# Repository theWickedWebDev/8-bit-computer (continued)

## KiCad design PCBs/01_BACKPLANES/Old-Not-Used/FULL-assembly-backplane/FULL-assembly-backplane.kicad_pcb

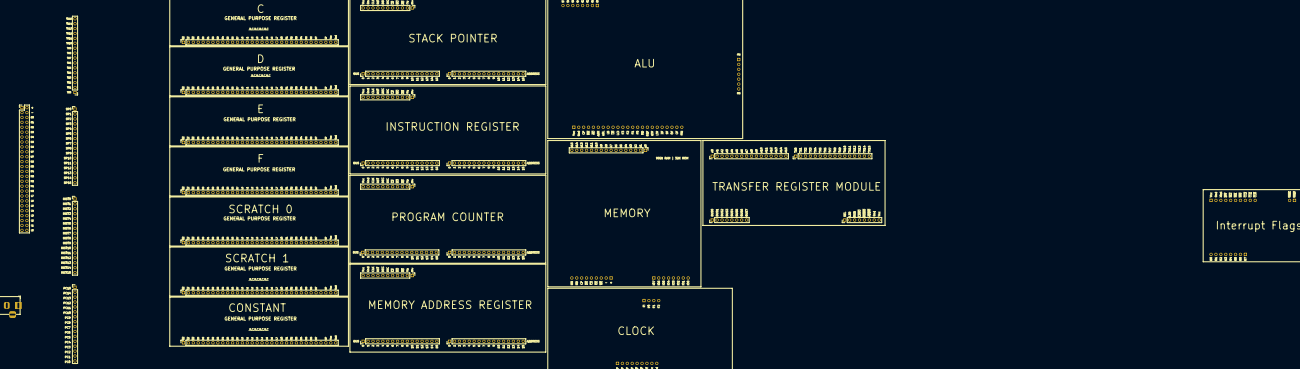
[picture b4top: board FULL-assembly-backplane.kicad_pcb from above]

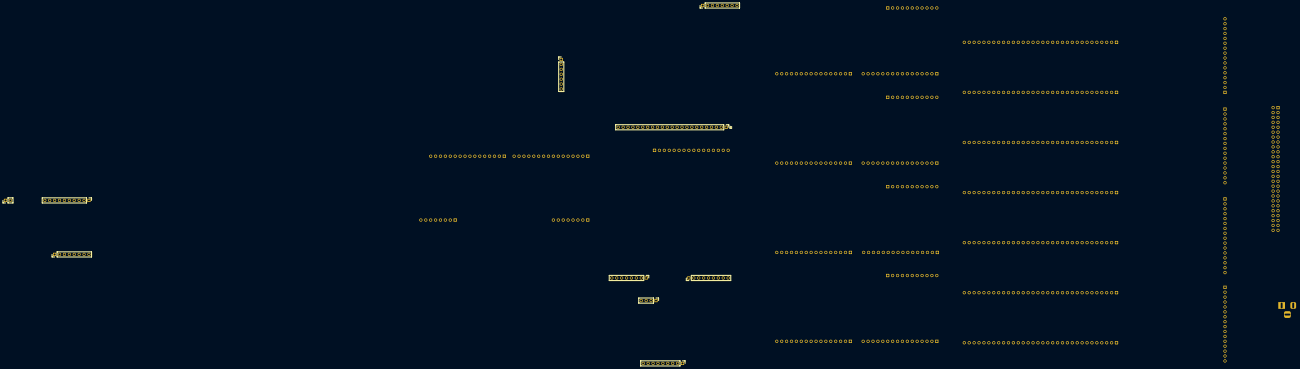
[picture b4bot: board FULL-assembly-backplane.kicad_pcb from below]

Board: 2 copper layers, 40 parts (10 on the bottom side), 108 nets, no tracks yet.

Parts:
J1, J2, J5, J6, J7, J8, J9, J10, J11, J12, J13, J14, J15, J16, J17: Conn_01x16; PinHeader_1x16_P2.54mm_Vertical
J1#2, J2#2: Conn_01x09; PinHeader_1x09_P2.54mm_Vertical
J1#3, J2#3, J2#5, J3, J4: Conn_01x08; PinHeader_1x08_P2.54mm_Vertical
J1#4: Conn_01x04; PinHeader_1x04_P2.54mm_Vertical
J1#5: Conn_01x10; PinHeader_1x10_P2.54mm_Vertical
J2#4: Conn_01x23; PinHeader_1x23_P2.54mm_Vertical
J3#2: Conn_01x07; PinHeader_1x07_P2.54mm_Vertical
J3#3: Conn_01x02; PinHeader_1x02_P2.54mm_Vertical
J18, J19, J20, J21: Conn_01x11; PinHeader_1x11_P2.54mm_Vertical
J25, J26, J32, J33, J34, J35, J36: Conn_01x32; PinSocket_1x32_P2.54mm_Vertical
J37: Conn_01x26; PinHeader_2x26_P2.54mm_Vertical
J43: Barrel_Jack; BarrelJack_Horizontal

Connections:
/IN_B0: J10.1, J11.1
/IN_B1: J10.2, J11.2
/IN_B2: J10.3, J11.3
/IN_B3: J10.4, J11.4
/IN_B4: J10.5, J11.5
/IN_B5: J10.6, J11.6
/IN_B6: J10.7, J11.7
/IN_B7: J10.8, J11.8
/IN_B8: J10.9, J11.9
/IN_B9: J10.10, J11.10
/IN_B10: J10.11, J11.11
/IN_B11: J10.12, J11.12
/IN_B12: J10.13, J11.13
/IN_B13: J10.14, J11.14
/IN_B14: J10.15, J11.15
/IN_B15: J10.16, J11.16
/MAR_B0: J16.1, J17.1
/MAR_B1: J16.2, J17.2
/MAR_B2: J16.3, J17.3
/MAR_B3: J16.4, J17.4
/MAR_B4: J16.5, J17.5
/MAR_B5: J16.6, J17.6
/MAR_B6: J16.7, J17.7
/MAR_B7: J16.8, J17.8
/MAR_B8: J16.9, J17.9
/MAR_B9: J16.10, J17.10
/MAR_B10: J16.11, J17.11
/MAR_B11: J16.12, J17.12
/MAR_B12: J16.13, J17.13
/MAR_B13: J16.14, J17.14
/MAR_B14: J16.15, J17.15
/MAR_B15: J16.16, J17.16
/PC_B0: J13.1, J14.1
/PC_B1: J13.2, J14.2
/PC_B2: J13.3, J14.3
/PC_B3: J13.4, J14.4
/PC_B4: J13.5, J14.5
/PC_B5: J13.6, J14.6
/PC_B6: J13.7, J14.7
/PC_B7: J13.8, J14.8
/PC_B8: J13.9, J14.9
/PC_B9: J13.10, J14.10
/PC_B10: J13.11, J14.11
/PC_B11: J13.12, J14.12
/PC_B12: J13.13, J14.13
/PC_B13: J13.14, J14.14
/PC_B14: J13.15, J14.15
/PC_B15: J13.16, J14.16
/SP_B0: J7.1, J8.1
/SP_B1: J7.2, J8.2
/SP_B2: J7.3, J8.3
/SP_B3: J7.4, J8.4
/SP_B4: J7.5, J8.5
/SP_B5: J7.6, J8.6
/SP_B6: J7.7, J8.7
/SP_B7: J7.8, J8.8
/SP_B8: J7.9, J8.9
/SP_B9: J7.10, J8.10
/SP_B10: J7.11, J8.11
/SP_B11: J7.12, J8.12
/SP_B12: J7.13, J8.13
/SP_B13: J7.14, J8.14
/SP_B14: J7.15, J8.15
/SP_B15: J7.16, J8.16
/TX0: J2.1, J5.1
/TX1: J2.2, J5.2
/TX2: J2.3, J5.3
/TX3: J2.4, J5.4
/TX4: J2.5, J5.5
/TX5: J2.6, J5.6
/TX6: J2.7, J5.7
/TX7: J2.8, J5.8
/TX8: J2.9, J5.9
/TX9: J2.10, J5.10
/TX10: J2.11, J5.11
/TX11: J2.12, J5.12
/TX12: J2.13, J5.13
/TX13: J2.14, J5.14
/TX14: J2.15, J5.15
/TX15: J2.16, J5.16
BUS0: J3.1, J25.5, J26.5, J32.5, J33.5, J34.5, J35.5, J36.5, J37.5, J37.6
BUS1: J3.2, J25.6, J26.6, J32.6, J33.6, J34.6, J35.6, J36.6, J37.7, J37.8
BUS2: J3.3, J25.7, J26.7, J32.7, J33.7, J34.7, J35.7, J36.7, J37.9, J37.10
BUS3: J3.4, J25.8, J26.8, J32.8, J33.8, J34.8, J35.8, J36.8, J37.11, J37.12
BUS4: J3.5, J25.9, J26.9, J32.9, J33.9, J34.9, J35.9, J36.9, J37.13, J37.14
BUS5: J3.6, J25.10, J26.10, J32.10, J33.10, J34.10, J35.10, J36.10, J37.15, J37.16
BUS6: J3.7, J25.11, J26.11, J32.11, J33.11, J34.11, J35.11, J36.11, J37.17, J37.18
BUS7: J3.8, J25.12, J26.12, J32.12, J33.12, J34.12, J35.12, J36.12, J37.19, J37.20
CLOCK: J18.9, J19.9, J20.9, J21.9, J25.30, J26.30, J32.30, J33.30, J34.30, J35.30, J36.30
GND: J4.7, J18.10, J19.10, J20.10, J21.10, J25.32, J26.32, J32.32, J33.32, J34.32, J35.32, J36.32, J37.3, J37.4, J43.2
L0: J1.1, J6.1, J9.1, J12.1, J15.1, J25.13, J26.13, J32.13, J33.13, J34.13, J35.13, J36.13, J37.51, J37.52
L1: J1.2, J6.2, J9.2, J12.2, J15.2, J25.14, J26.14, J32.14, J33.14, J34.14, J35.14, J36.14, J37.49, J37.50
L2: J1.3, J6.3, J9.3, J12.3, J15.3, J25.15, J26.15, J32.15, J33.15, J34.15, J35.15, J36.15, J37.47, J37.48
L3: J1.4, J6.4, J9.4, J12.4, J15.4, J25.16, J26.16, J32.16, J33.16, J34.16, J35.16, J36.16, J37.45, J37.46
L4: J1.5, J6.5, J9.5, J12.5, J15.5, J25.17, J26.17, J32.17, J33.17, J34.17, J35.17, J36.17, J37.43, J37.44
L5: J1.6, J6.6, J9.6, J12.6, J15.6, J25.18, J26.18, J32.18, J33.18, J34.18, J35.18, J36.18, J37.41, J37.42
L6: J1.7, J6.7, J9.7, J12.7, J15.7, J25.19, J26.19, J32.19, J33.19, J34.19, J35.19, J36.19, J37.39, J37.40
L7: J1.8, J6.8, J9.8, J12.8, J15.8, J25.20, J26.20, J32.20, J33.20, J34.20, J35.20, J36.20, J37.37, J37.38
M0: J1.9, J6.9, J9.9, J12.9, J15.9, J25.21, J26.21, J32.21, J33.21, J34.21, J35.21, J36.21, J37.35, J37.36
M1: J1.10, J6.10, J9.10, J12.10, J15.10, J25.22, J26.22, J32.22, J33.22, J34.22, J35.22, J36.22, J37.33, J37.34
M2: J1.11, J6.11, J9.11, J12.11, J15.11, J25.23, J26.23, J32.23, J33.23, J34.23, J35.23, J36.23, J37.31, J37.32
M3: J1.12, J6.12, J9.12, J12.12, J15.12, J25.24, J26.24, J32.24, J33.24, J34.24, J35.24, J36.24, J37.29, J37.30
M4: J1.13, J6.13, J9.13, J12.13, J15.13, J25.25, J26.25, J32.25, J33.25, J34.25, J35.25, J36.25, J37.27, J37.28
M5: J1.14, J6.14, J9.14, J12.14, J15.14, J25.26, J26.26, J32.26, J33.26, J34.26, J35.26, J36.26, J37.25, J37.26
M6: J1.15, J6.15, J9.15, J12.15, J15.15, J25.27, J26.27, J32.27, J33.27, J34.27, J35.27, J36.27, J37.23, J37.24
M7: J1.16, J6.16, J9.16, J12.16, J15.16, J25.28, J26.28, J32.28, J33.28, J34.28, J35.28, J36.28, J37.21, J37.22
RESET: J18.8, J19.8, J20.8, J21.8
VCC: J4.8, J18.11, J19.11, J20.11, J21.11, J25.31, J26.31, J32.31, J33.31, J34.31, J35.31, J36.31, J37.1, J37.2, J43.1

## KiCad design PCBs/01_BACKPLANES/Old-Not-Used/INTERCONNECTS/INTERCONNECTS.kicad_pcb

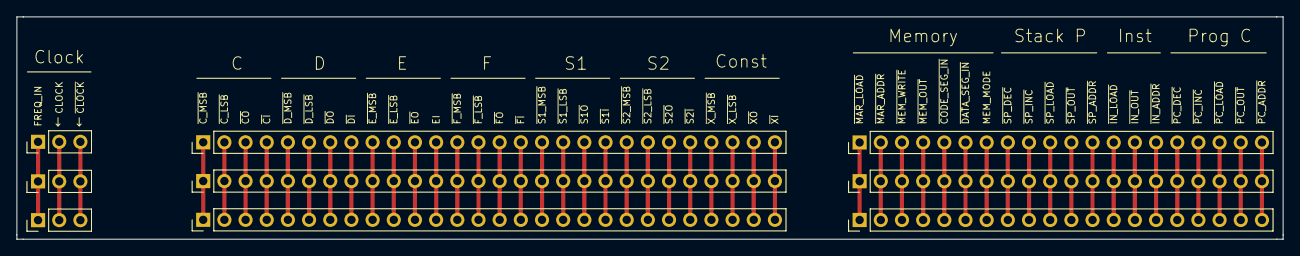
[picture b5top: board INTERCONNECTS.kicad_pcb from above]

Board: 2 copper layers, 151.9 x 26.7 mm, 9 parts (0 on the bottom side), 51 nets.

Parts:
J1, J2, J3: Conn_01x03; PinHeader_1x03_P2.54mm_Vertical
J4, J5, J6: Conn_01x28; PinHeader_1x28_P2.54mm_Vertical
J7, J8, J9: Conn_01x20; PinHeader_1x20_P2.54mm_Vertical

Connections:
unnamed: J1.1, J2.1, J3.1
unnamed: J1.2, J2.2, J3.2
unnamed: J1.3, J2.3, J3.3
unnamed: J4.1, J5.1, J6.1
unnamed: J4.2, J5.2, J6.2
unnamed: J4.3, J5.3, J6.3
unnamed: J4.4, J5.4, J6.4
unnamed: J4.5, J5.5, J6.5
unnamed: J4.6, J5.6, J6.6
unnamed: J4.7, J5.7, J6.7
unnamed: J4.8, J5.8, J6.8
unnamed: J4.9, J5.9, J6.9
unnamed: J4.10, J5.10, J6.10
unnamed: J4.11, J5.11, J6.11
unnamed: J4.12, J5.12, J6.12
unnamed: J4.13, J5.13, J6.13
unnamed: J4.14, J5.14, J6.14
unnamed: J4.15, J5.15, J6.15
unnamed: J4.16, J5.16, J6.16
unnamed: J4.17, J5.17, J6.17
unnamed: J4.18, J5.18, J6.18
unnamed: J4.19, J5.19, J6.19
unnamed: J4.20, J5.20, J6.20
unnamed: J4.21, J5.21, J6.21
unnamed: J4.22, J5.22, J6.22
unnamed: J4.23, J5.23, J6.23
unnamed: J4.24, J5.24, J6.24
unnamed: J4.25, J5.25, J6.25
unnamed: J4.26, J5.26, J6.26
unnamed: J4.27, J5.27, J6.27
unnamed: J4.28, J5.28, J6.28
unnamed: J7.1, J8.1, J9.1
unnamed: J7.2, J8.2, J9.2
unnamed: J7.3, J8.3, J9.3
unnamed: J7.4, J8.4, J9.4
unnamed: J7.5, J8.5, J9.5
unnamed: J7.6, J8.6, J9.6
unnamed: J7.7, J8.7, J9.7
unnamed: J7.8, J8.8, J9.8
unnamed: J7.9, J8.9, J9.9
unnamed: J7.10, J8.10, J9.10
unnamed: J7.11, J8.11, J9.11
unnamed: J7.12, J8.12, J9.12
unnamed: J7.13, J8.13, J9.13
unnamed: J7.14, J8.14, J9.14
unnamed: J7.15, J8.15, J9.15
unnamed: J7.16, J8.16, J9.16
unnamed: J7.17, J8.17, J9.17
unnamed: J7.18, J8.18, J9.18
unnamed: J7.19, J8.19, J9.19
unnamed: J7.20, J8.20, J9.20

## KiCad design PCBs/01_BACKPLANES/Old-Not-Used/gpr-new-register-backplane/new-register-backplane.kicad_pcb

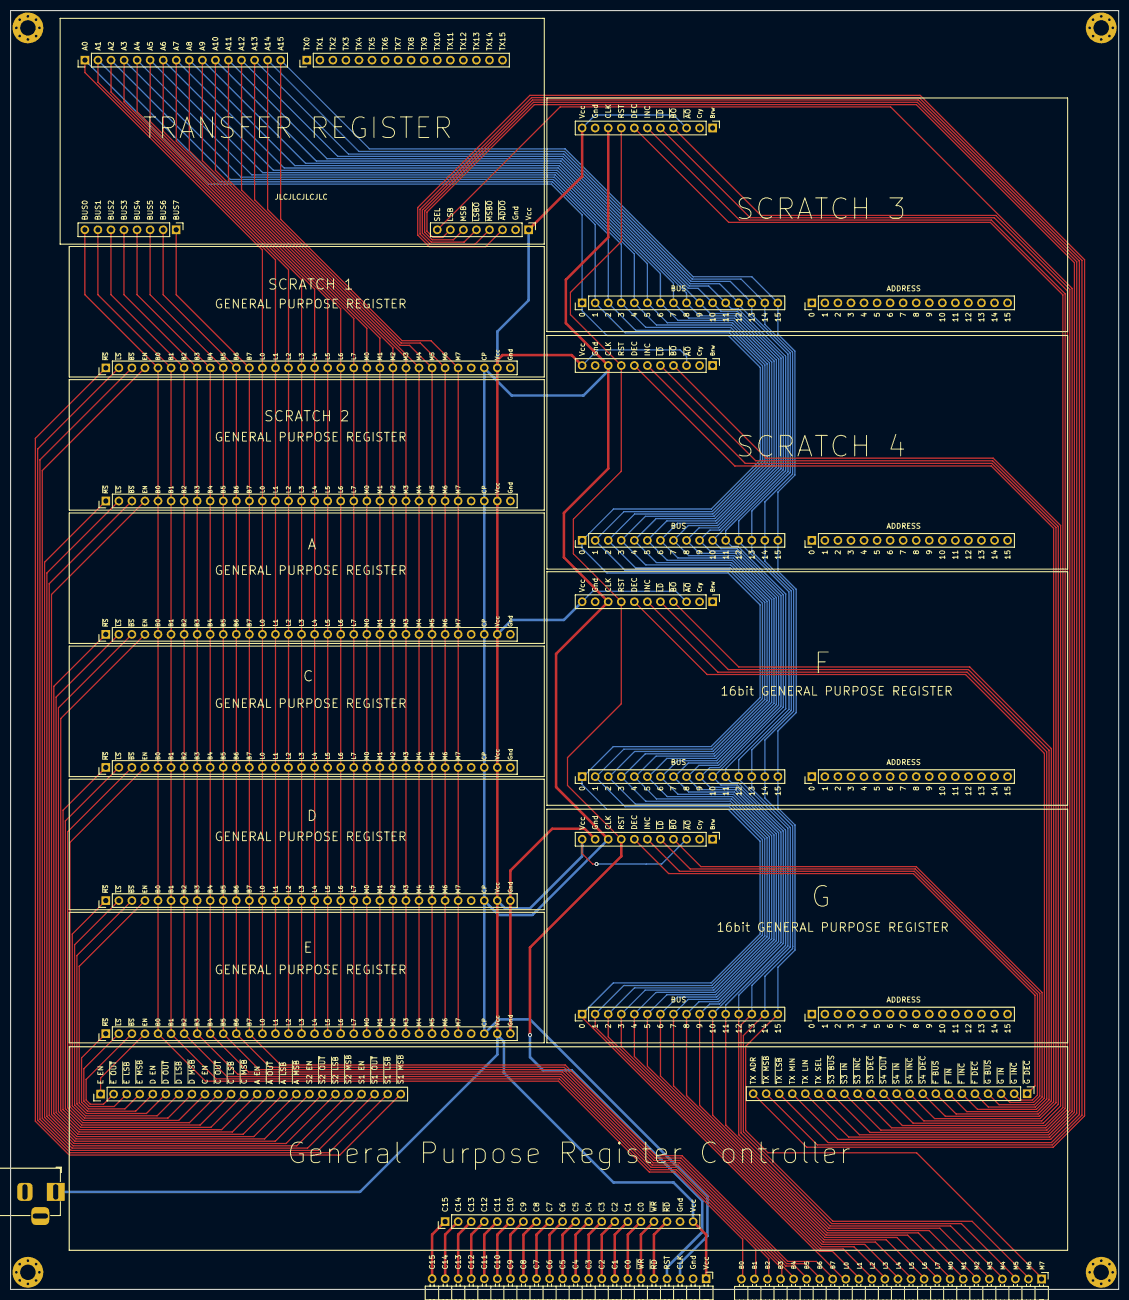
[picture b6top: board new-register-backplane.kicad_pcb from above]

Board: 2 copper layers, 215.7 x 248.9 mm, 28 parts (0 on the bottom side), 92 nets.

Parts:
J1: Conn_01x22; PinHeader_1x22_P2.54mm_Horizontal
J2: Conn_01x20; PinHeader_1x20_P2.54mm_Vertical
J3, J5, J6, J7, J8, J9: Conn_01x32; PinHeader_1x32_P2.54mm_Vertical
J4: Conn_01x24; PinHeader_1x24_P2.54mm_Horizontal
J10, J15, J18, J21: Conn_01x11; PinHeader_1x11_P2.54mm_Vertical
J11, J12, J13, J14, J16, J17, J19, J20, J23, J24: Conn_01x16; PinHeader_1x16_P2.54mm_Vertical
J22, J25: Conn_01x08; PinHeader_1x08_P2.54mm_Vertical
J28: Conn_01x22; PinHeader_1x22_P2.54mm_Vertical
J29: Conn_01x24; PinHeader_1x24_P2.54mm_Vertical
J31: Barrel_Jack_MountingPin; BarrelJack_Horizontal

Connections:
B0: J3.5, J4.24, J5.5, J6.5, J7.5, J8.5, J9.5, J22.8
B1: J3.6, J4.23, J5.6, J6.6, J7.6, J8.6, J9.6, J22.7
B2: J3.7, J4.22, J5.7, J6.7, J7.7, J8.7, J9.7, J22.6
B3: J3.8, J4.21, J5.8, J6.8, J7.8, J8.8, J9.8, J22.5
B4: J3.9, J4.20, J5.9, J6.9, J7.9, J8.9, J9.9, J22.4
B5: J3.10, J4.19, J5.10, J6.10, J7.10, J8.10, J9.10, J22.3
B6: J3.11, J4.18, J5.11, J6.11, J7.11, J8.11, J9.11, J22.2
B7: J3.12, J4.17, J5.12, J6.12, J7.12, J8.12, J9.12, J22.1
C0: J1.7, J2.16
C1: J1.8, J2.15
C2: J1.9, J2.14
C3: J1.10, J2.13
C4: J1.11, J2.12
C5: J1.12, J2.11
C6: J1.13, J2.10
C7: J1.14, J2.9
C8: J1.15, J2.8
C9: J1.16, J2.7
C10: J1.17, J2.6
C11: J1.18, J2.5
C12: J1.19, J2.4
C13: J1.20, J2.3
C14: J1.21, J2.2
C15: J1.22, J2.1
CLOCK: J1.3, J3.30, J5.30, J6.30, J7.30, J8.30, J9.30, J10.9, J15.9, J18.9, J21.9
EN_A: J3.4, J29.13
EN_C: J5.4, J29.9
EN_D: J6.4, J29.5
EN_E: J7.4, J29.1
EN_S1: J8.4, J29.21
EN_S2: J9.4, J29.17
GND: J1.2, J2.19, J3.32, J5.32, J6.32, J7.32, J8.32, J9.32, J10.10, J15.10, J18.10, J21.10, J25.2, J31.2
L0: J3.13, J4.16, J5.13, J6.13, J7.13, J8.13, J9.13, J11.1, J13.1, J17.1, J20.1, J24.1
L1: J3.14, J4.15, J5.14, J6.14, J7.14, J8.14, J9.14, J11.2, J13.2, J17.2, J20.2, J24.2
L2: J3.15, J4.14, J5.15, J6.15, J7.15, J8.15, J9.15, J11.3, J13.3, J17.3, J20.3, J24.3
L3: J3.16, J4.13, J5.16, J6.16, J7.16, J8.16, J9.16, J11.4, J13.4, J17.4, J20.4, J24.4
L4: J3.17, J4.12, J5.17, J6.17, J7.17, J8.17, J9.17, J11.5, J13.5, J17.5, J20.5, J24.5
L5: J3.18, J4.11, J5.18, J6.18, J7.18, J8.18, J9.18, J11.6, J13.6, J17.6, J20.6, J24.6
L6: J3.19, J4.10, J5.19, J6.19, J7.19, J8.19, J9.19, J11.7, J13.7, J17.7, J20.7, J24.7
L7: J3.20, J4.9, J5.20, J6.20, J7.20, J8.20, J9.20, J11.8, J13.8, J17.8, J20.8, J24.8
M0: J3.21, J4.8, J5.21, J6.21, J7.21, J8.21, J9.21, J11.9, J13.9, J17.9, J20.9, J24.9
M1: J3.22, J4.7, J5.22, J6.22, J7.22, J8.22, J9.22, J11.10, J13.10, J17.10, J20.10, J24.10
M2: J3.23, J4.6, J5.23, J6.23, J7.23, J8.23, J9.23, J11.11, J13.11, J17.11, J20.11, J24.11
M3: J3.24, J4.5, J5.24, J6.24, J7.24, J8.24, J9.24, J11.12, J13.12, J17.12, J20.12, J24.12
M4: J3.25, J4.4, J5.25, J6.25, J7.25, J8.25, J9.25, J11.13, J13.13, J17.13, J20.13, J24.13
M5: J3.26, J4.3, J5.26, J6.26, J7.26, J8.26, J9.26, J11.14, J13.14, J17.14, J20.14, J24.14
M6: J3.27, J4.2, J5.27, J6.27, J7.27, J8.27, J9.27, J11.15, J13.15, J17.15, J20.15, J24.15
M7: J3.28, J4.1, J5.28, J6.28, J7.28, J8.28, J9.28, J11.16, J13.16, J17.16, J20.16, J24.16
RESET: J1.4, J10.8, J15.8, J18.8, J21.8
TX_BUS_SELECT: J25.8, J28.17
TX_LATCH_LSB: J25.7, J28.18
TX_LATCH_MSB: J25.6, J28.19
VCC: J1.1, J2.20, J3.31, J5.31, J6.31, J7.31, J8.31, J9.31, J10.3, J10.11, J15.3, J15.11, J18.3, J18.11, J21.3, J21.11, J25.1, J31.1
~BO_F: J18.4, J28.8
~BO_G: J21.4, J28.4
~BO_S3: J10.4, J28.16
~BO_S4: J15.4, J28.12
~BS_A: J3.3, J29.14
~BS_C: J5.3, J29.10
~BS_D: J6.3, J29.6
~BS_E: J7.3, J29.2
~BS_S1: J8.3, J29.22
~BS_S2: J9.3, J29.18
~DEC_F: J18.7, J28.5
~DEC_G: J21.7, J28.1
~DEC_S3: J10.7, J28.13
~DEC_S4: J15.7, J28.9
~INC_F: J18.6, J28.6
~INC_G: J21.6, J28.2
~INC_S3: J10.6, J28.14
~INC_S4: J15.6, J28.10
~LD_F: J18.5, J28.7
~LD_G: J21.5, J28.3
~LD_S3: J10.5, J28.15
~LD_S4: J15.5, J28.11
~LS_A: J3.2, J29.15
~LS_C: J5.2, J29.11
~LS_D: J6.2, J29.7
~LS_E: J7.2, J29.3
~LS_S1: J8.2, J29.23
~LS_S2: J9.2, J29.19
~MS_A: J3.1, J29.16
~MS_C: J5.1, J29.12
~MS_D: J6.1, J29.8
~MS_E: J7.1, J29.4
~MS_S1: J8.1, J29.24
~MS_S2: J9.1, J29.20
~RD: J1.5, J2.18
~TX_ASSERT_ADDRESS: J25.3, J28.22
~TX_ASSERT_LSB_MAIN: J25.5, J28.20
~TX_ASSERT_MSB_MAIN: J25.4, J28.21
~WR: J1.6, J2.17
